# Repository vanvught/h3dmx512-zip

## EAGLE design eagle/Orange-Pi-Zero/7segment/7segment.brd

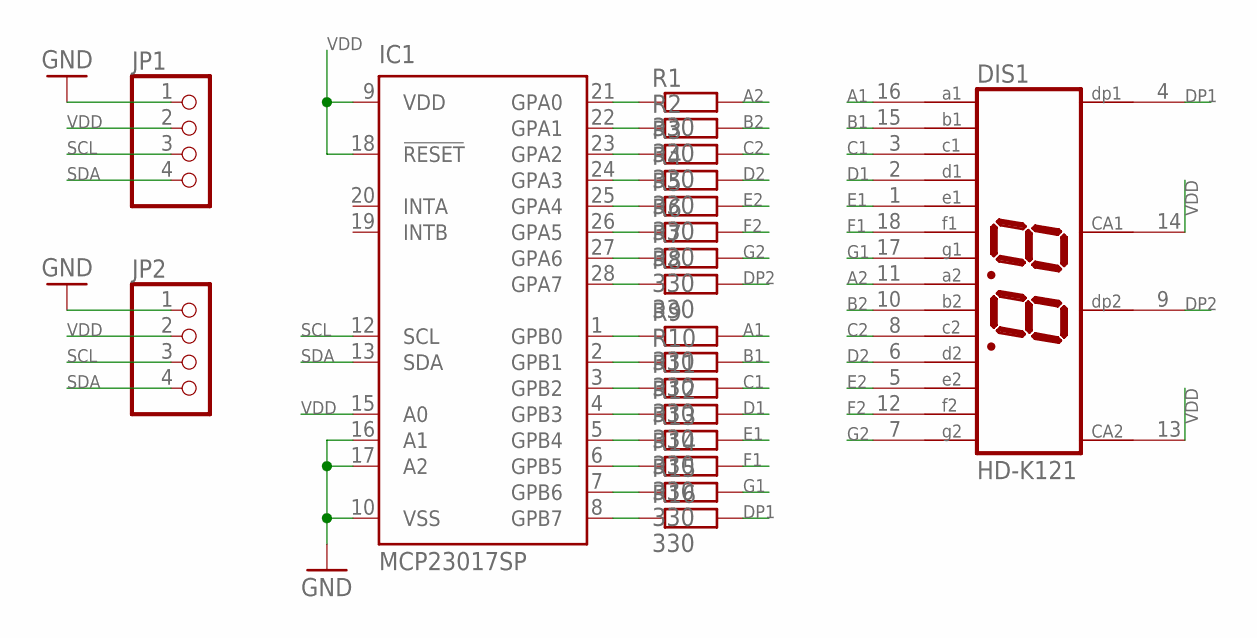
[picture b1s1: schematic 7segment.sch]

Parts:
DIS1: HD-K121; HDSP-R
IC1: MCP23017SP; DIL28-3
JP1, JP2: PINHD-1X4; 1X04
R1, R2, R3, R4, R5, R6, R7, R8, R9, R10, R11, R12, R13, R14, R15, R16: 330; 0204V

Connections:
A1: DIS1.16 (A1), R9.2
A2: DIS1.11 (A2), R1.2
B1: DIS1.15 (B1), R10.2
B2: DIS1.10 (B2), R2.2
C1: DIS1.3 (C1), R11.2
C2: DIS1.8 (C2), R3.2
D1: DIS1.2 (D1), R12.2
D2: DIS1.6 (D2), R4.2
DP1: DIS1.4 (DP1), R16.2
DP2: DIS1.9 (DP2), R8.2
E1: DIS1.1 (E1), R13.2
E2: DIS1.5 (E2), R5.2
F1: DIS1.18 (F1), R14.2
F2: DIS1.12 (F2), R6.2
G1: DIS1.17 (G1), R15.2
G2: DIS1.7 (G2), R7.2
GND: IC1.10 (VSS), IC1.16 (A1), IC1.17 (A2), JP1.1, JP2.1
unnamed: IC1.21 (GPA0), R1.1
unnamed: IC1.22 (GPA1), R2.1
unnamed: IC1.23 (GPA2), R3.1
unnamed: IC1.24 (GPA3), R4.1
unnamed: IC1.25 (GPA4), R5.1
unnamed: IC1.26 (GPA5), R6.1
unnamed: IC1.27 (GPA6), R7.1
unnamed: IC1.28 (GPA7), R8.1
unnamed: IC1.1 (GPB0), R9.1
unnamed: IC1.2 (GPB1), R10.1
unnamed: IC1.3 (GPB2), R11.1
unnamed: IC1.4 (GPB3), R12.1
unnamed: IC1.5 (GPB4), R13.1
unnamed: IC1.6 (GPB5), R14.1
unnamed: IC1.7 (GPB6), R15.1
unnamed: IC1.8 (GPB7), R16.1
SCL: IC1.12 (SCL), JP1.3, JP2.3
SDA: IC1.13 (SDA), JP1.4, JP2.4
VDD: DIS1.13 (CA2), DIS1.14 (CA1), IC1.9 (VDD), IC1.15 (A0), IC1.18 (!RESET), JP1.2, JP2.2

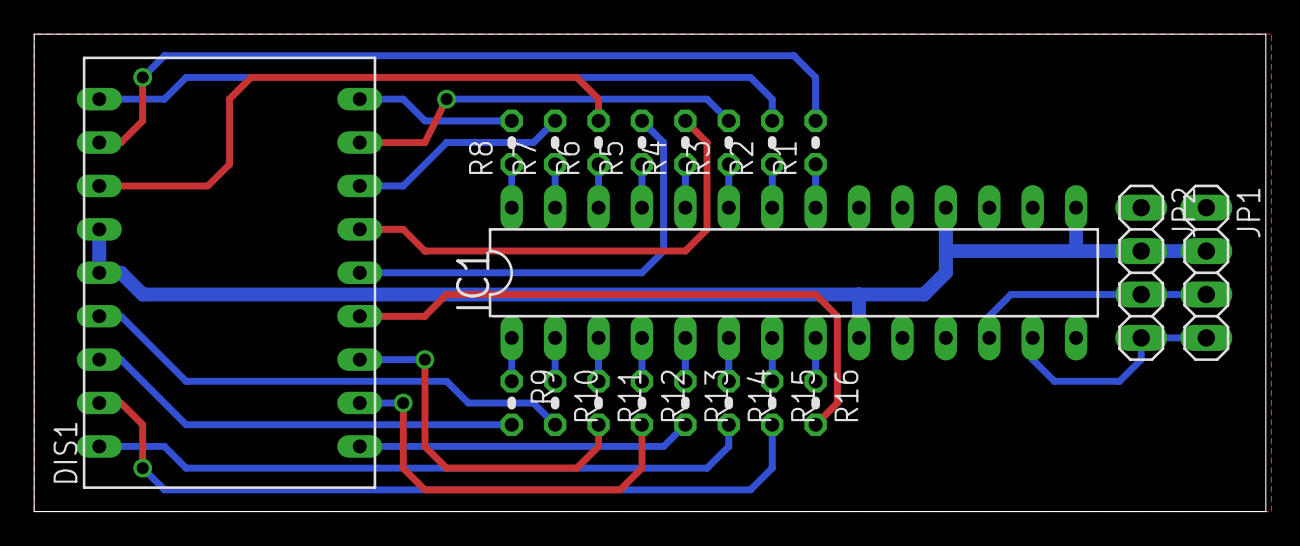
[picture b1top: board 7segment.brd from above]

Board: 2 copper layers, 72.1 x 27.9 mm, 20 parts (0 on the bottom side), 36 nets.

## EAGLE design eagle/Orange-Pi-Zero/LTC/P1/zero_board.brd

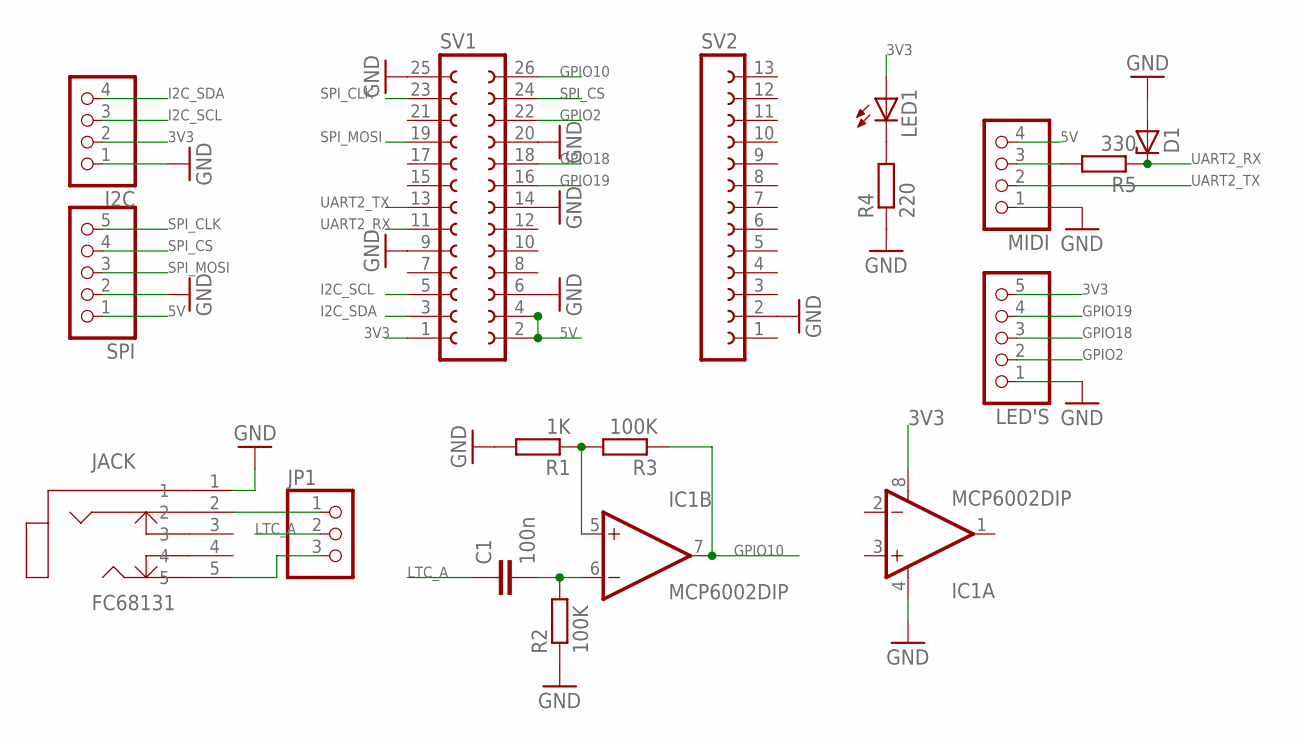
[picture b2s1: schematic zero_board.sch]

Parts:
C1: 100n; C050-024X044
D1: ZENER-DIODEZD-2.5; ZDIO-2.5
I2C: PINHD-1X4; 1X04
IC1: MCP6002DIP; DIP08
JACK: FC68131; FC68131-5P
JP1: PINHD-1X3; 1X03
LED1: LED3MM
LED'S: PINHD-1X5; 1X05
MIDI: PINHD-1X4; 1X04
R1: 1K; 0204/5
R2, R3: 100K; 0204/5
R4: 220; 0204/5
R5: 330; 0204V
SPI: PINHD-1X5; 1X05
SV1: FE13-2
SV2: FE13-1; FE13

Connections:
3V3: I2C.2, IC1.8 (V+), LED1.A, LED'S.5, SV1.1
5V: MIDI.4, SPI.1, SV1.2, SV1.4
GND: D1.A, I2C.1, IC1.4 (V-), JACK.1, LED'S.1, MIDI.1, R1.2, R2.1, R4.1, SPI.2, SV1.6, SV1.9, SV1.14, SV1.20, SV1.25, SV2.2
GPIO2: LED'S.2, SV1.22
GPIO10: IC1.7 (OUT), R3.1, SV1.26
GPIO18: LED'S.3, SV1.18
GPIO19: LED'S.4, SV1.16
I2C_SCL: I2C.3, SV1.5
I2C_SDA: I2C.4, SV1.3
LTC_A: C1.1, JP1.2
unnamed: LED1.K (C), R4.2
unnamed: JACK.5, JP1.3
unnamed: JACK.2, JP1.1
unnamed: C1.2, IC1.6 (-IN), R2.2
unnamed: IC1.5 (+IN), R1.1, R3.2
unnamed: MIDI.3, R5.2
SPI_CLK: SPI.5, SV1.23
SPI_CS: SPI.4, SV1.24
SPI_MOSI: SPI.3, SV1.19
UART2_RX: D1.C, R5.1, SV1.11
UART2_TX: MIDI.2, SV1.13

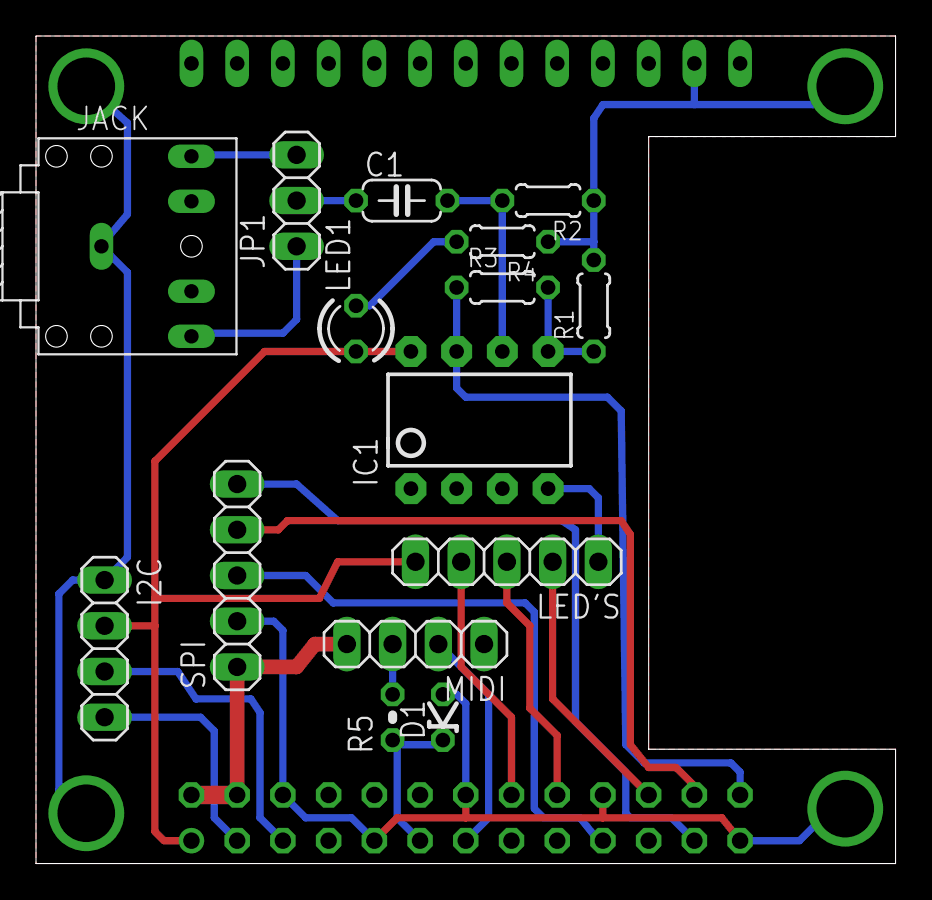
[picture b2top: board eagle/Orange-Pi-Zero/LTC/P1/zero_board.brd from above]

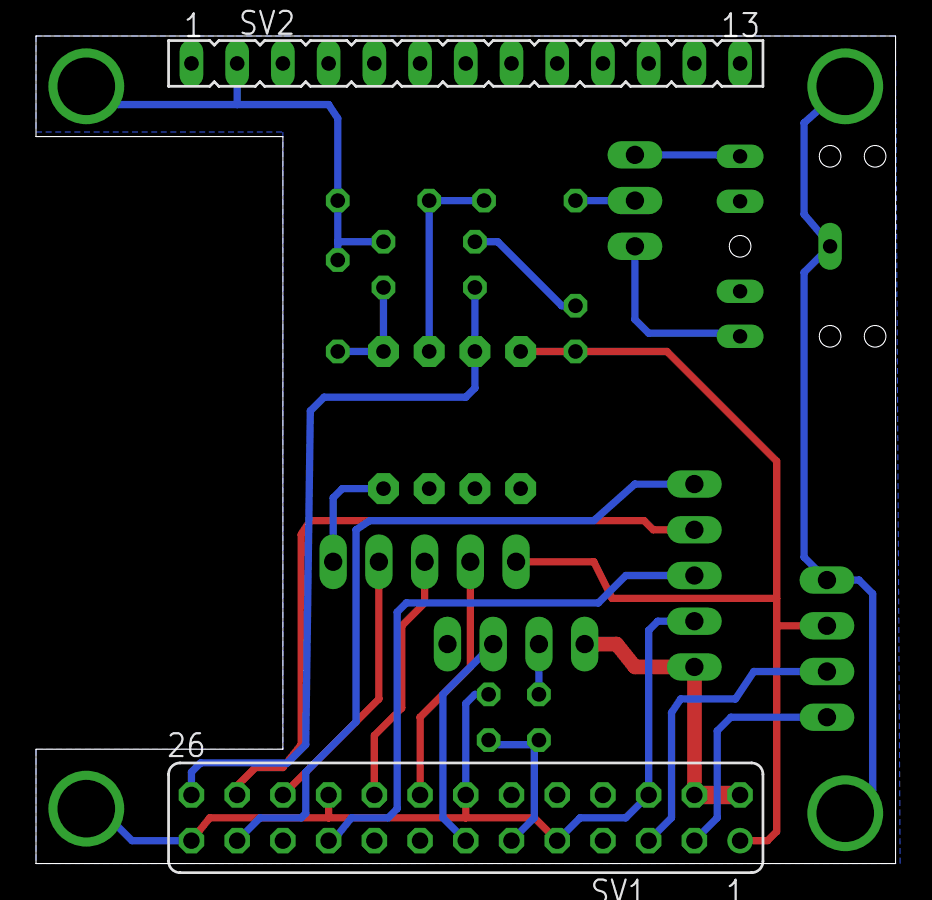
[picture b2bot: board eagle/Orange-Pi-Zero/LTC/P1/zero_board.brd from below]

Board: 2 copper layers, 47.8 x 46.0 mm, 17 parts (2 on the bottom side), 21 nets.

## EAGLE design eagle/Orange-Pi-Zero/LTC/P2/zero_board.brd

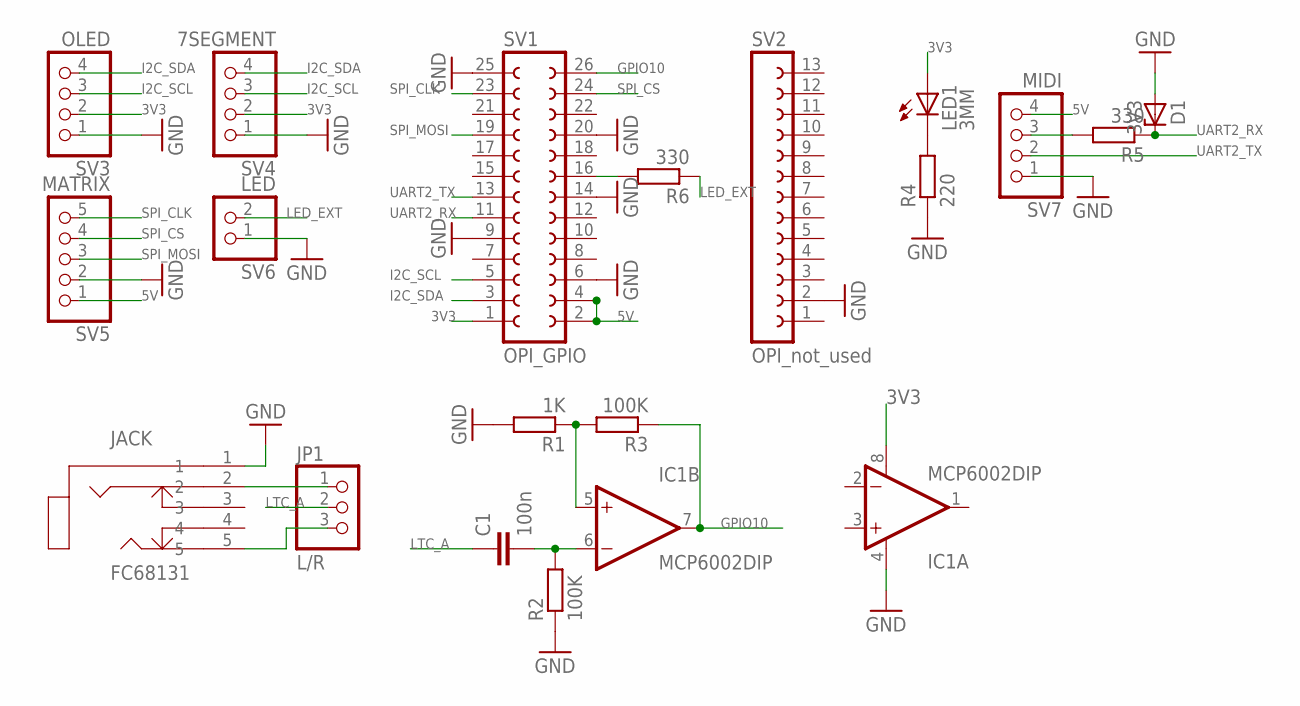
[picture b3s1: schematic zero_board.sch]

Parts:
C1: 100n; C050-024X044
D1: 3V3; ZDIO-2.5
IC1: MCP6002DIP; DIP08
JACK: FC68131; FC68131-5P
JP1: L/R; 1X03
LED1: 3MM; LED3MM
R1: 1K; 0204/5
R2, R3: 100K; 0204/5
R4: 220; 0204/5
R5, R6: 330; 0204V
SV1: OPI_GPIO; FE13-2
SV2: OPI_not_used; FE13
SV3: OLED; 1X04
SV4: 7SEGMENT; 1X04
SV5: MATRIX; 1X05
SV6: LED; 1X02
SV7: MIDI; 1X04

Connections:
3V3: IC1.8 (V+), LED1.A, SV1.1, SV3.2, SV4.2
5V: SV1.2, SV1.4, SV5.1, SV7.4
GND: D1.A, IC1.4 (V-), JACK.1, R1.2, R2.1, R4.1, SV1.6, SV1.9, SV1.14, SV1.20, SV1.25, SV2.2, SV3.1, SV4.1, SV5.2, SV6.1, SV7.1
GPIO10: IC1.7 (OUT), R3.1, SV1.26
I2C_SCL: SV1.5, SV3.3, SV4.3
I2C_SDA: SV1.3, SV3.4, SV4.4
LED_EXT: R6.1, SV6.2
LTC_A: C1.1, JP1.2
unnamed: LED1.K (C), R4.2
unnamed: JACK.5, JP1.3
unnamed: JACK.2, JP1.1
unnamed: R6.2, SV1.16
unnamed: C1.2, IC1.6 (-IN), R2.2
unnamed: IC1.5 (+IN), R1.1, R3.2
unnamed: R5.2, SV7.3
SPI_CLK: SV1.23, SV5.5
SPI_CS: SV1.24, SV5.4
SPI_MOSI: SV1.19, SV5.3
UART2_RX: D1.C, R5.1, SV1.11
UART2_TX: SV1.13, SV7.2

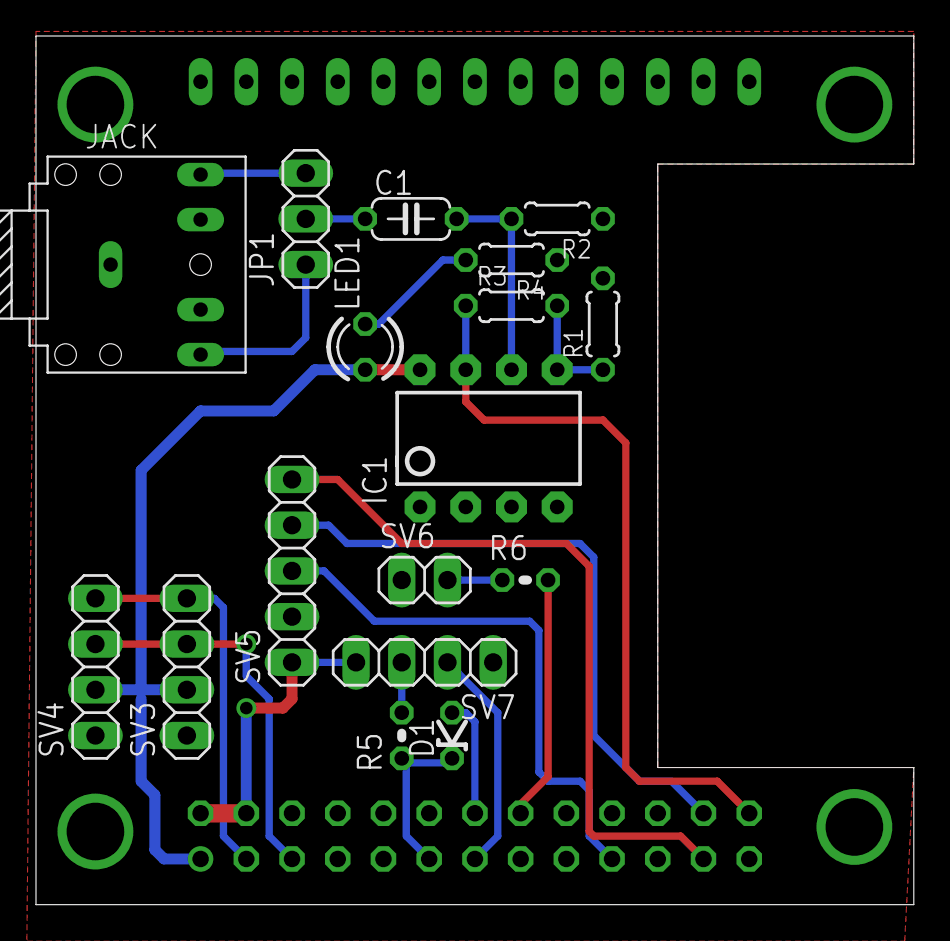
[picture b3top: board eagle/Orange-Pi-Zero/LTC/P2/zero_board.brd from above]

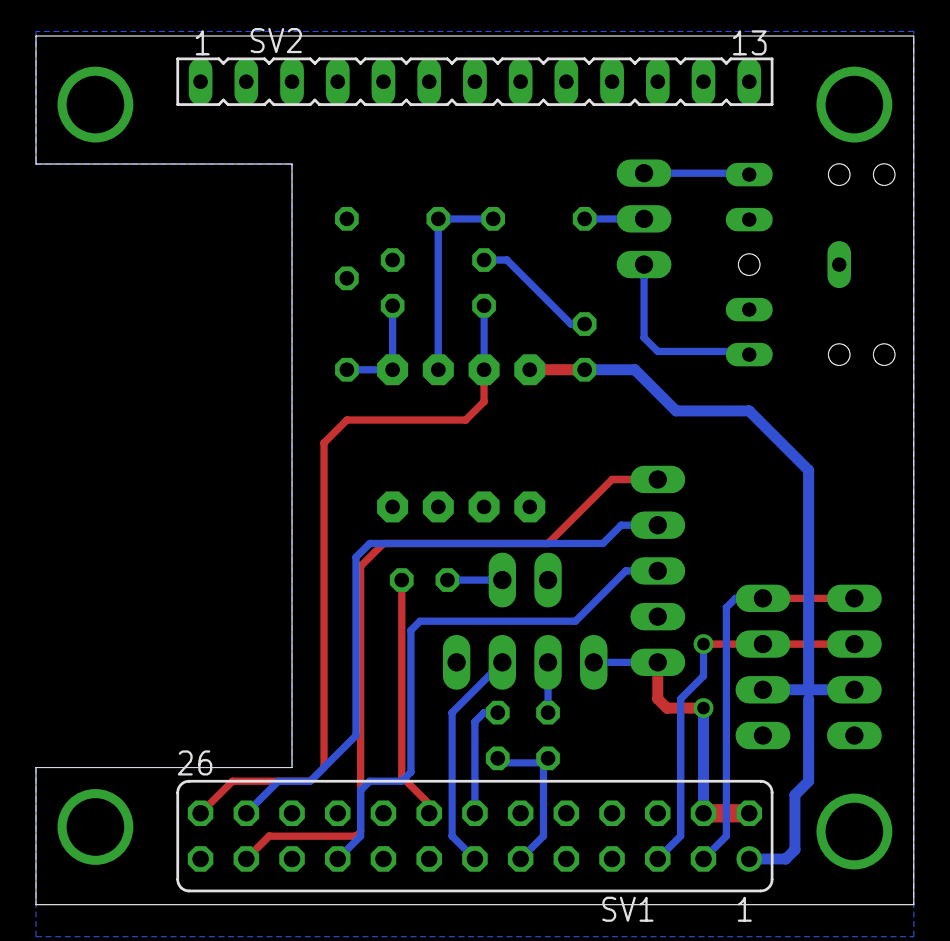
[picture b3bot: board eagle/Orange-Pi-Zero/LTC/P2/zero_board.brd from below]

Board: 2 copper layers, 48.8 x 48.3 mm, 19 parts (2 on the bottom side), 20 nets.

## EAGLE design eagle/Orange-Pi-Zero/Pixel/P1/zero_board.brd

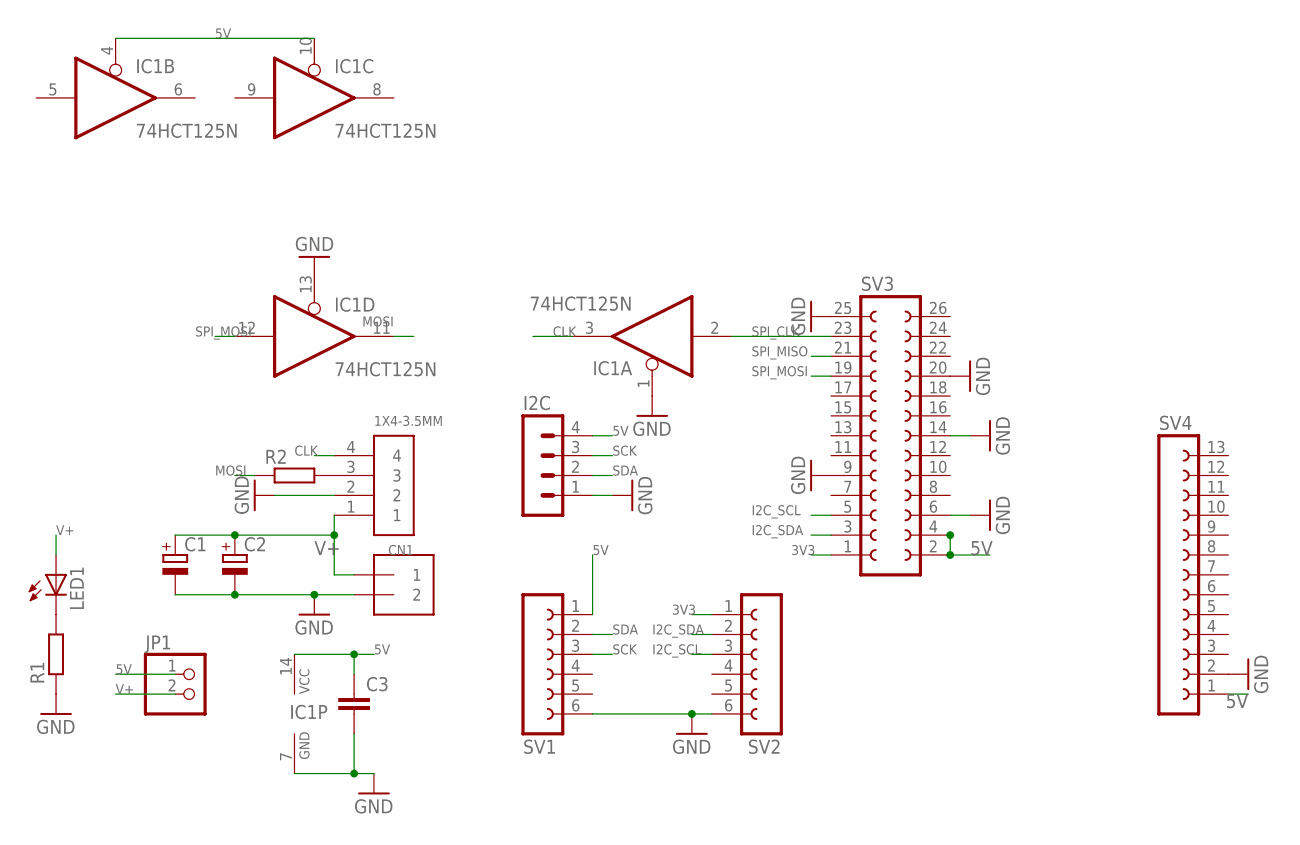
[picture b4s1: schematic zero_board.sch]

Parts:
C1, C2: CPOL-EUE5-6; E5-6
C3: C-EU050-024X044; C050-024X044
CN1: 1X4-3.5MM; 1X04-3.5MM
I2C: MA04-1
IC1: 74HCT125N; DIL14
J1: 1X2-3.5MM
JP1: PINHD-1X2; 1X02
LED1: LED3MM
R1, R2: R-EU_0204/5; 0204/5
SV1, SV2: FE06-1; FE06
SV3: FE13-2
SV4: FE13-1; FE13

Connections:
3V3: SV2.1, SV3.1
5V: C3.1, I2C.4, IC1.4 (OE), IC1.10 (OE), IC1.14 (VCC), JP1.1, SV1.1, SV3.2, SV3.4, SV4.1
CLK: CN1.4, IC1.3 (O)
GND: C1.-, C2.-, C3.2, CN1.2, I2C.1, IC1.1 (OE), IC1.7 (GND), IC1.13 (OE), J1.2, R1.1, SV1.6, SV2.6, SV3.6, SV3.9, SV3.14, SV3.20, SV3.25, SV4.2
I2C_SCL: SV2.3, SV3.5
I2C_SDA: SV2.2, SV3.3
MOSI: IC1.11 (O), R2.1
unnamed: LED1.K (C), R1.2
unnamed: CN1.3, R2.2
SCK: I2C.3, SV1.3
SDA: I2C.2, SV1.2
SPI_CLK: IC1.2 (I), SV3.23
SPI_MISO: SV3.21
SPI_MOSI: IC1.12 (I), SV3.19
V+: C1.+, C2.+, CN1.1, J1.1, JP1.2, LED1.A

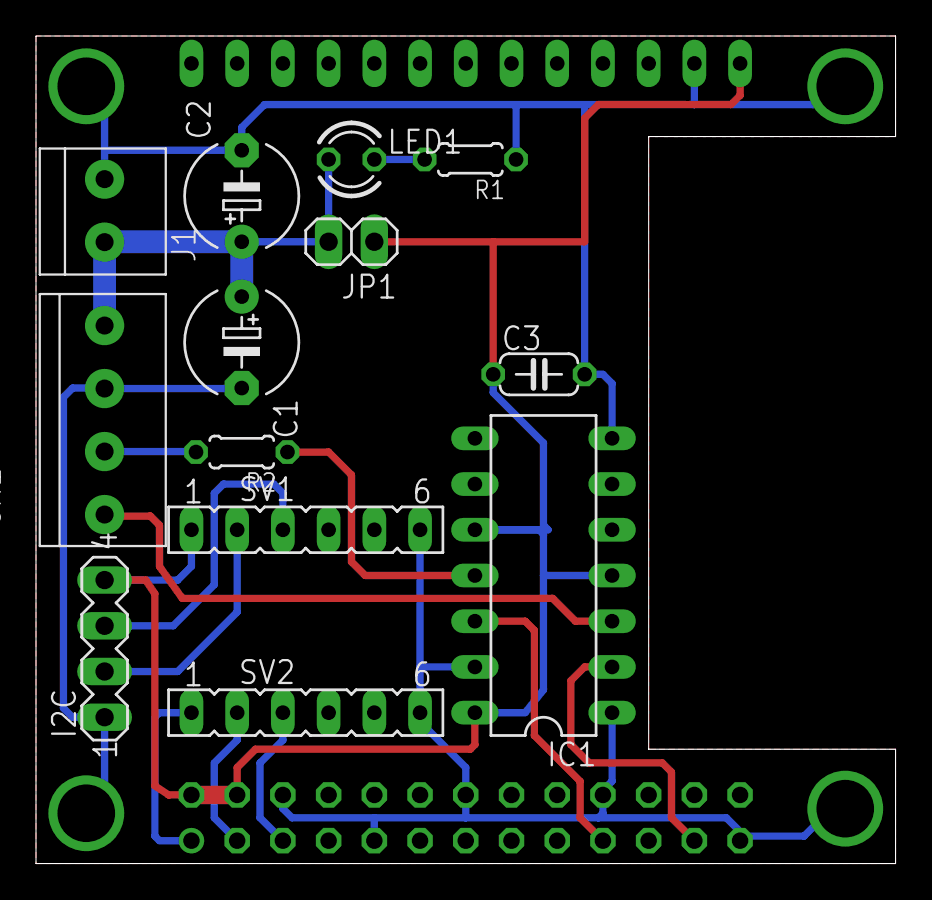
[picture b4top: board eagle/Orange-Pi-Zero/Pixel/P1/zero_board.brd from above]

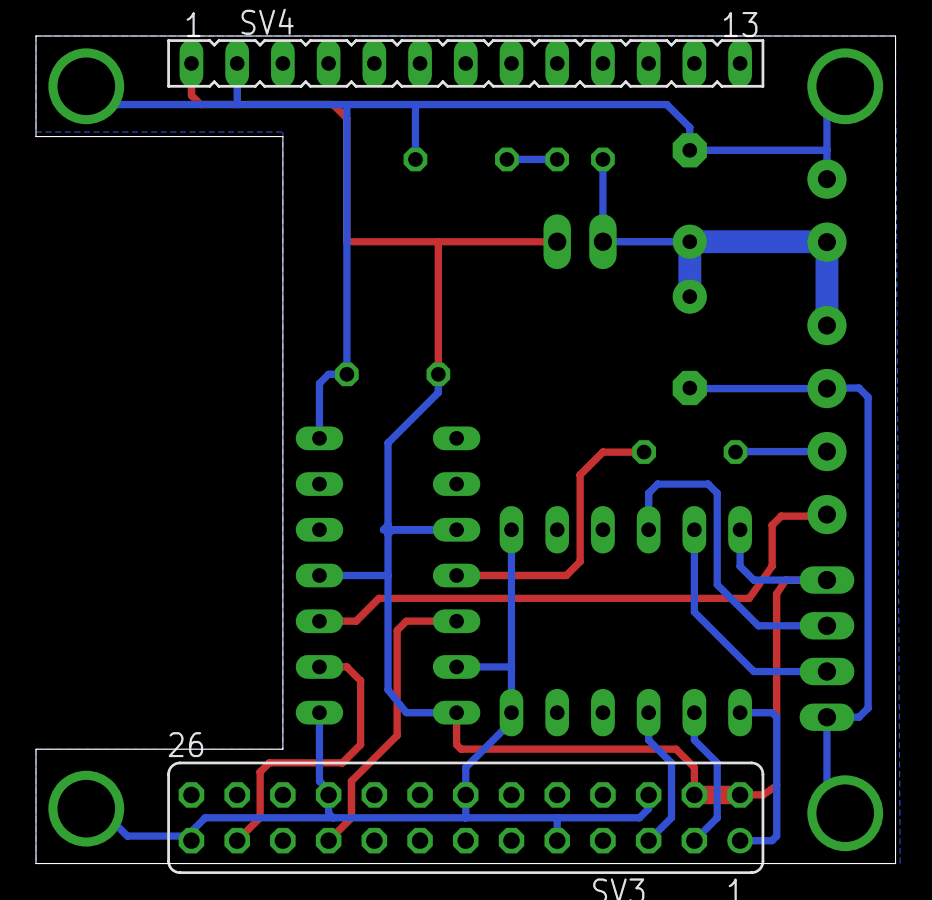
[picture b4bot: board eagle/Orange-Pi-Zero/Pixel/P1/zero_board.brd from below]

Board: 2 copper layers, 47.8 x 46.0 mm, 15 parts (2 on the bottom side), 14 nets.

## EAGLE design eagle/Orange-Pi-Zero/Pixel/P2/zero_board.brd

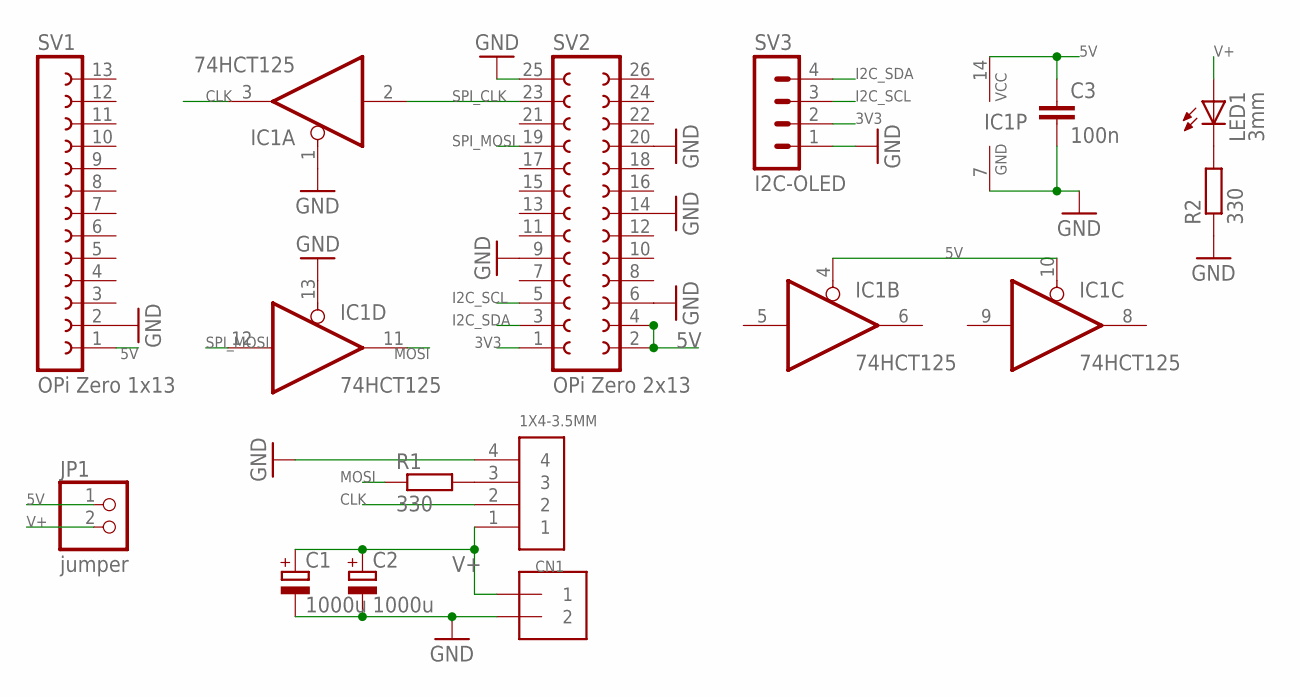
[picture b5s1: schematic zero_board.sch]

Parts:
C1, C2: 1000u; E5-6
C3: 100n; C050-024X044
CN1: 1X4-3.5MM; 1X04-3.5MM
IC1: 74HCT125; DIL14
J1: 1X2-3.5MM
JP1: jumper; 1X02
LED1: 3mm; LED3MM
R1, R2: 330; 0204/7
SV1: OPi Zero 1x13; FE13
SV2: OPi Zero 2x13; FE13-2
SV3: I2C-OLED; MA04-1

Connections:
3V3: SV2.1, SV3.2
5V: C3.1, IC1.4 (OE), IC1.10 (OE), IC1.14 (VCC), JP1.1, SV1.1, SV2.2, SV2.4
CLK: CN1.2, IC1.3 (O)
GND: C1.-, C2.-, C3.2, CN1.4, IC1.1 (OE), IC1.7 (GND), IC1.13 (OE), J1.2, R2.1, SV1.2, SV2.6, SV2.9, SV2.14, SV2.20, SV2.25, SV3.1
I2C_SCL: SV2.5, SV3.3
I2C_SDA: SV2.3, SV3.4
MOSI: IC1.11 (O), R1.1
unnamed: LED1.K (C), R2.2
unnamed: CN1.3, R1.2
SPI_CLK: IC1.2 (I), SV2.23
SPI_MOSI: IC1.12 (I), SV2.19
V+: C1.+, C2.+, CN1.1, J1.1, JP1.2, LED1.A

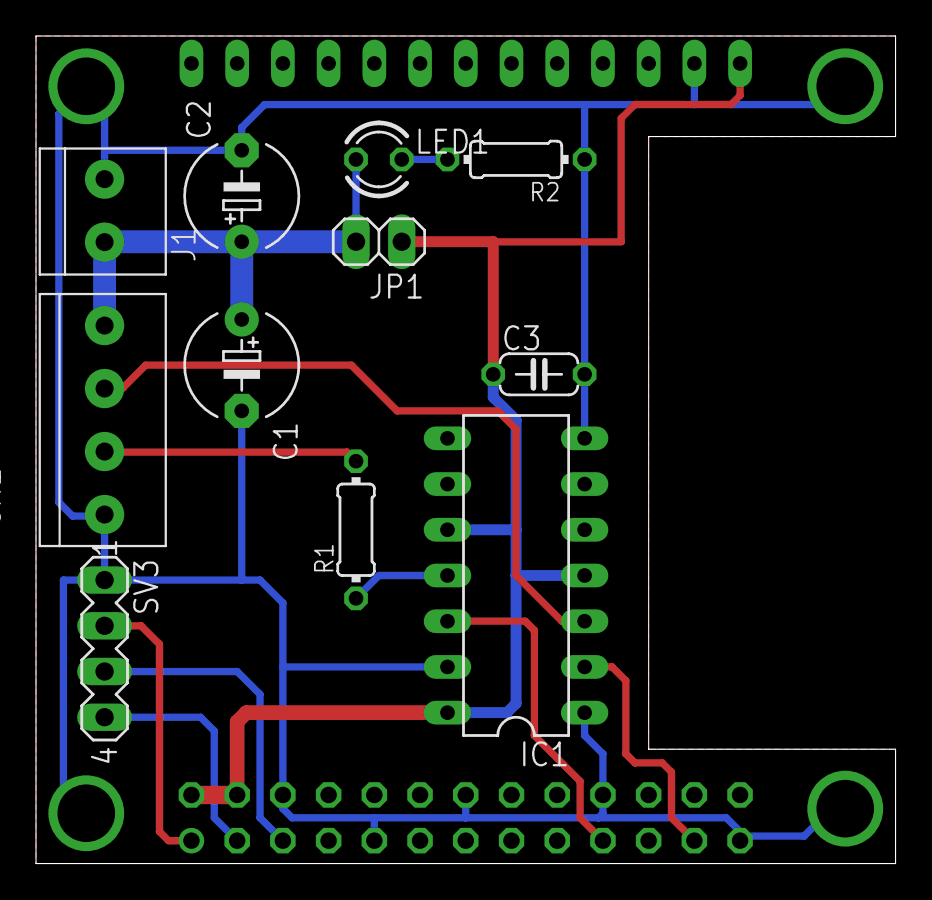
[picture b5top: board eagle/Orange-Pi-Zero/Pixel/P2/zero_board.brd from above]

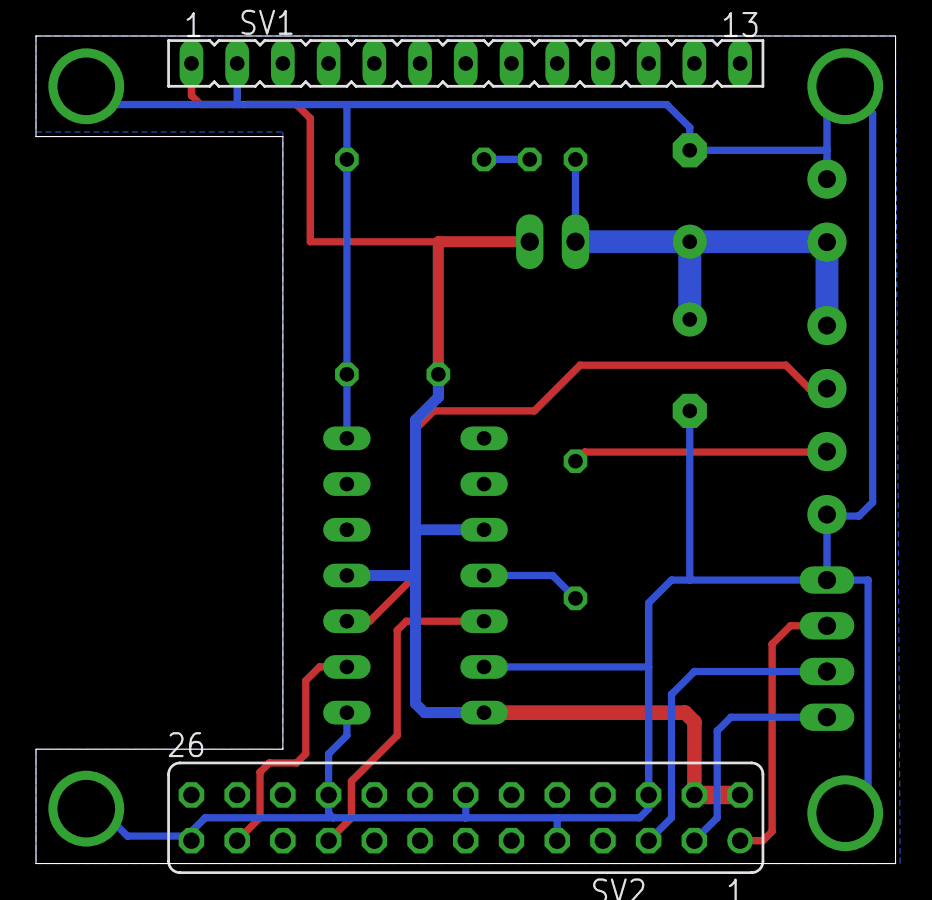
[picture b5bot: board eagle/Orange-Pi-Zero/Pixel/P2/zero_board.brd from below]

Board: 2 copper layers, 47.8 x 46.0 mm, 13 parts (2 on the bottom side), 12 nets.

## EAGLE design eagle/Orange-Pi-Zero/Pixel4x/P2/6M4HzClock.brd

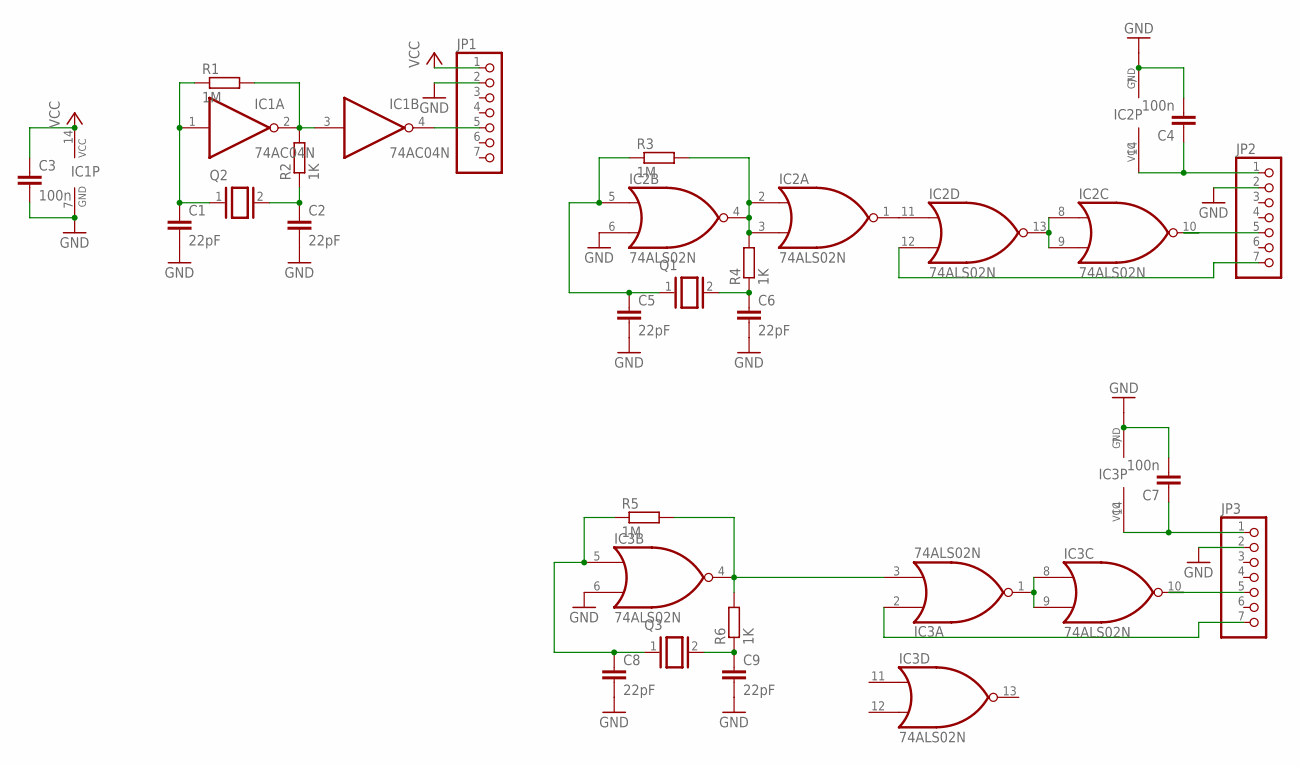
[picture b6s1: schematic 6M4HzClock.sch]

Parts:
C1, C2, C5, C6, C8, C9: 22pF; C025-024X044
C3, C4, C7: 100n; C050-024X044
IC1: 74AC04N; DIL14
IC2, IC3: 74ALS02N; DIL14
JP1, JP2, JP3: PINHD-1X7; 1X07
Q1, Q2, Q3: XTAL/S; QS
R1, R3, R5: 1M; 0204V
R2, R4, R6: 1K; 0204V

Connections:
6.4MHZ: IC1.4 (O), JP1.5
6.4MHZ/02: IC2.1 (O), IC2.11 (I0)
6.4MHZ/OUT: IC2.10 (O), JP2.5
6.4MHZ/OUT1: IC3.10 (O), JP3.5
ENN: IC2.12 (I1), JP2.7
ENN1: IC3.2 (I0), JP3.7
GND: C1.2, C2.2, C3.2, C5.2, C6.2, C8.2, C9.2, IC1.7 (GND), IC2.6 (I1), IC2.7 (GND), IC3.6 (I1), IC3.7 (GND), JP1.2, JP2.2, JP3.2
unnamed: C1.1, IC1.1 (I), Q2.1, R1.1
unnamed: IC1.2 (O), IC1.3 (I), R1.2, R2.2
unnamed: C2.1, Q2.2, R2.1
unnamed: IC2.2 (I0), IC2.3 (I1), IC2.4 (O), R3.2, R4.2
unnamed: IC2.8 (I0), IC2.9 (I1), IC2.13 (O)
unnamed: IC3.3 (I1), IC3.4 (O), R5.2, R6.2
unnamed: C5.1, IC2.5 (I0), Q1.1, R3.1
unnamed: C6.1, Q1.2, R4.1
unnamed: C8.1, IC3.5 (I0), Q3.1, R5.1
unnamed: C9.1, Q3.2, R6.1
unnamed: IC3.1 (O), IC3.8 (I0), IC3.9 (I1)
VCC: C3.1, IC1.14 (VCC), JP1.1
VCC/01: C7.1, IC3.14 (VCC), JP3.1
VCC/02: C4.1, IC2.14 (VCC), JP2.1

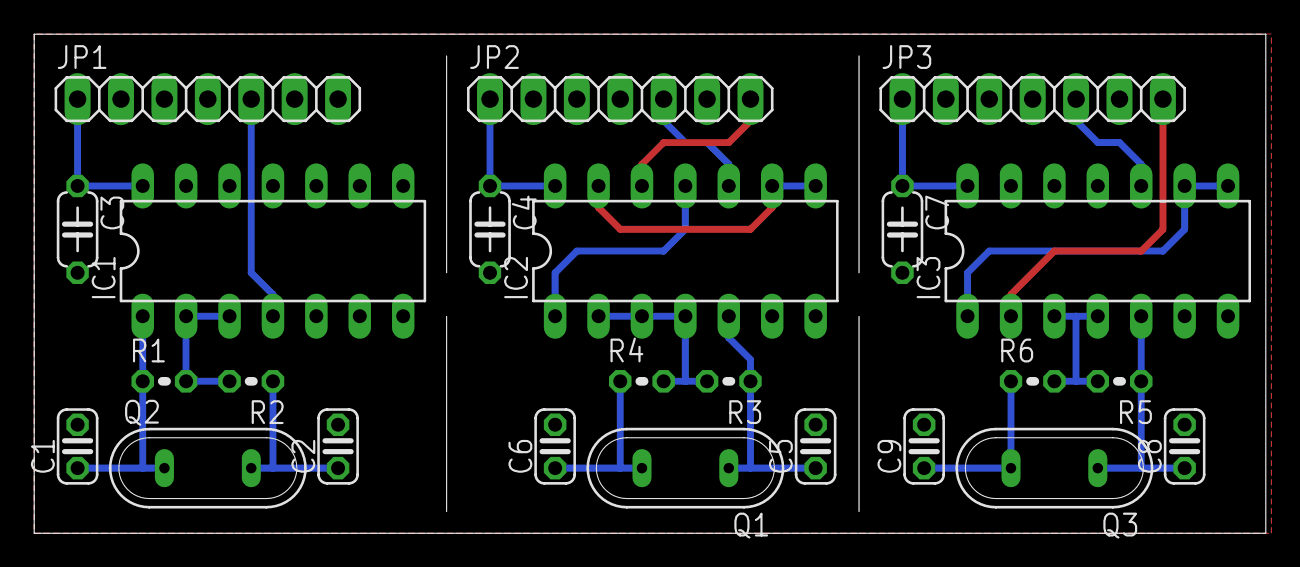
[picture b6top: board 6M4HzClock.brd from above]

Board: 2 copper layers, 72.1 x 29.2 mm, 24 parts (0 on the bottom side), 21 nets.

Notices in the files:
parts and their libraries:
SparkFun-Connectors: Licensing: Creative Commons ShareAlike 4.0 International - https://creativecommons.org/licenses/by-sa/4.0
